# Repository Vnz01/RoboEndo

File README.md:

# How to use?

## Using Two Adafruit M0 Boards

## Receiver MCU:

Program Receiver Side using the code found in /Receiver/ECE using Arduino IDE then plug in to your computer that will be connected to the Maxon Motors

> Optionally you can also do a quick program on platformio using the RF_Head Libary to just quickly read the data and print to serial. I made the switch from Arduino IDE to Platformio mid project, hence why Receiver is programmed through Arduino and Transmitter on platformio

## Transmitter MCU:

Program Transmitter Side using the code found in /Transmitter using Platformio

Edit Latency, I found 10 to work the best giving the controller and receiver to have the best performance.

## Pinout

En - Gnd: Slide Switch (Power Enabling)

13 - Gnd: Lock Switch (Position Control)

12 - Gnd: Momentary Button (Forward)

11 - Gnd: Momentary Button (Backward)

10 - Gnd: Analog Stick Switch (Start Button)

9 - Gnd: Power LED

6 - Gnd: Charging LED

3V3 - Analog Stick Power

GND - Analog Stick GND

A0 - Analog Stick X

A1 - Analog Stick Y

## Computer Side

Using Linux Ubuntu 20.04, install ROS2 Noetic. Download catkin. Following the readme inside /Catheter-Control-main/src/README.md, install the official EPOS Linux Driver. Check the EPOS Command Library PDF. I found the drivers on the japanese maxon motor website after looking at their products. EPOS Studio is for downloading drivers straight to the motors. Then you will be using catkin build not catkin_make to access all the directories. So following the other README located in /Catheter-Control-main/README.md scroll to the bottom. Copy the src file in /Catheter-Control-main to the src file created by catkin build and run your catkin build. To edit the code, look inside the Catheter-Control-main and find control_test.py and edit the if else conditional where NEW CONTROLLER is located.

## ROS Commands

Source the files -
source ~/catkin_ws/devel/setup.bash

Start ROS -
roslaunch maxon_epos_example example_maxon_epos.launch

Run ROSPY -
rosrun maxon_epos_example control_test.py

## Left Off

Controller working properly, there is commented code for a scroll wheel. Pins can be defined to any open pin. It adds to the existing string sent over serial. All the code just needs to be uncommented once scroll wheel is attached.

For the catheter side, look in Catheter-Control-main/src/maxon-epos-example/scripts/old/control_test.py

This file is the edited file and the one we use to control the catheter as we don't have libraries for the main control.py. In this file this is where it is defined for all the movements. To use the controller on your own file it is very modular, just make sure to read input from serial which is a constant string of data that just needs to be parsed.

I left off at implementing the new motor 5 for retracting and protracting. I included a 5th motor in the configuration file in motor_hd.yaml. To implement this, looking inside maxon_epos_driver it seems that it checks how many motors are included and sends commands. You need to define in maxon_epos_example how these commands are sent over ROS and how it will control the 5th motor.

Essentially to get a grasp of this I would restart on a new control_test.py and just read serial values sent by the controller, and try to redefine each movement instead of following the work I have.

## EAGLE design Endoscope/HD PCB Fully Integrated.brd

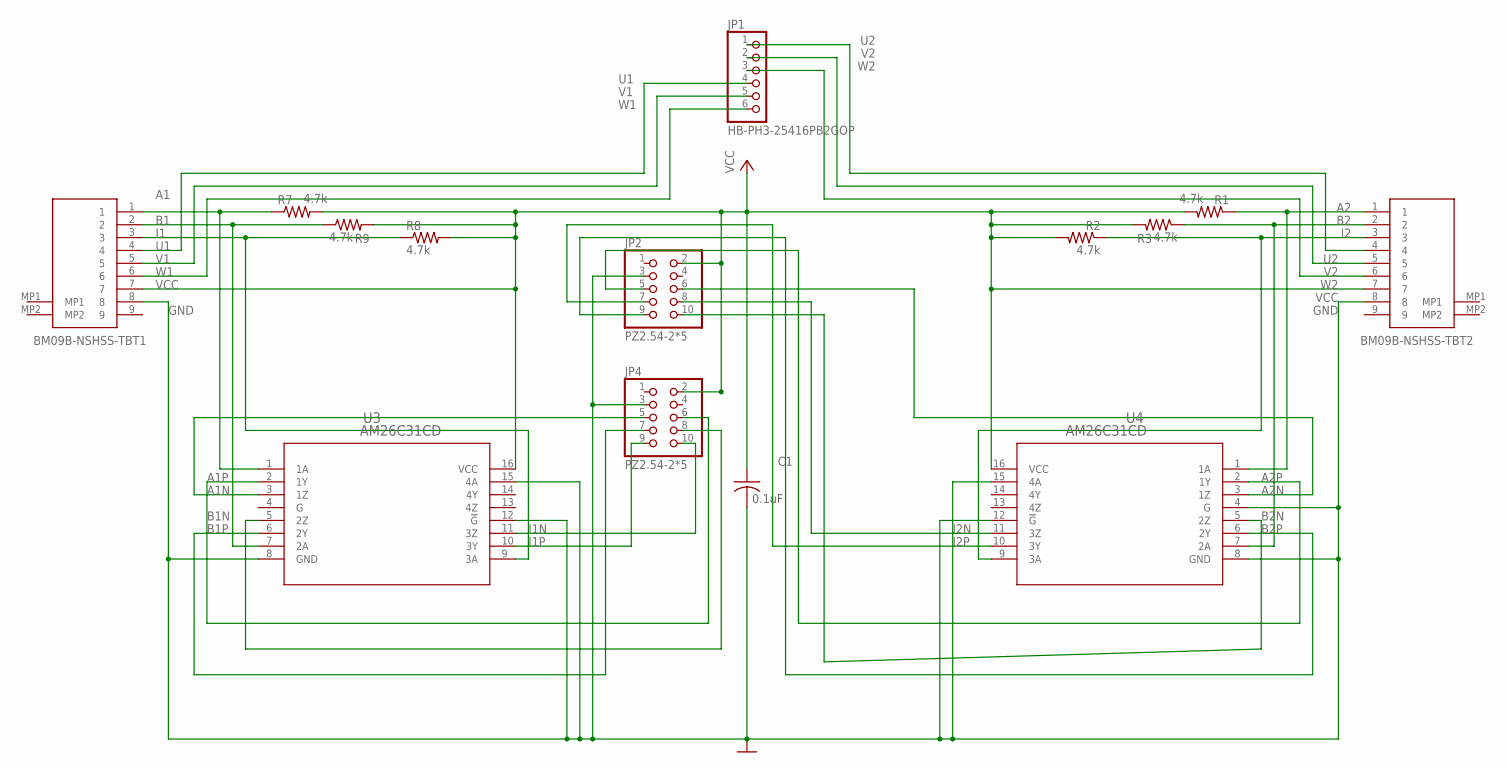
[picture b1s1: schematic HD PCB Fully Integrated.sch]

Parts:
BM09B-NSHSS-TBT1, BM09B-NSHSS-TBT2: BM09B-NSHSS-TBT_LF__SN_; BM09BNSHSSTBTLFSN
C1: 0.1uF; C0805
JP1: HB-PH3-25416PB2GOP; 1X06
JP2, JP4: PZ2.54-2*5; 2X05
R1, R2, R3, R7, R8, R9: 4.7k; R0805; MPN CRCW04024K70FKED
U3, U4: AM26C31CD; D16

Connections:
A1: BM09B-NSHSS-TBT1.1, R7.1, U3.1 (1A)
A1N: JP4.5, U3.3 (1Z)
A1P: JP4.6, U3.2 (1Y)
A2: BM09B-NSHSS-TBT2.1, R1.1, U4.1 (1A)
A2N: JP2.6, U4.3 (1Z)
A2P: JP2.5, U4.2 (1Y)
B1: BM09B-NSHSS-TBT1.2, R9.1, U3.7 (2A)
B1N: JP4.8, U3.5 (2Z)
B1P: JP4.7, U3.6 (2Y)
B2: BM09B-NSHSS-TBT2.2, R3.1, U4.7 (2A)
B2N: JP2.10, U4.5 (2Z)
B2P: JP2.9, U4.6 (2Y)
GND: BM09B-NSHSS-TBT1.8, BM09B-NSHSS-TBT2.8, C1.2, JP2.3, JP4.3, U3.8 (GND), U3.12 (!G), U3.15 (4A), U4.4 (G), U4.8 (GND), U4.12 (!G), U4.15 (4A)
I1: BM09B-NSHSS-TBT1.3, R8.1, U3.9 (3A)
I1N: JP4.10, U3.11 (3Z)
I1P: JP4.9, U3.10 (3Y)
I2: BM09B-NSHSS-TBT2.3, R2.1, U4.9 (3A)
I2N: JP2.8, U4.11 (3Z)
I2P: JP2.7, U4.10 (3Y)
U1: BM09B-NSHSS-TBT1.4, JP1.4
U2: BM09B-NSHSS-TBT2.4, JP1.1
V1: BM09B-NSHSS-TBT1.5, JP1.5
V2: BM09B-NSHSS-TBT2.5, JP1.2
VCC: BM09B-NSHSS-TBT1.7, BM09B-NSHSS-TBT2.7, C1.1, JP2.2, JP4.2, R1.2, R2.2, R3.2, R7.2, R8.2, R9.2, U3.16 (VCC), U4.16 (VCC)
W1: BM09B-NSHSS-TBT1.6, JP1.6
W2: BM09B-NSHSS-TBT2.6, JP1.3

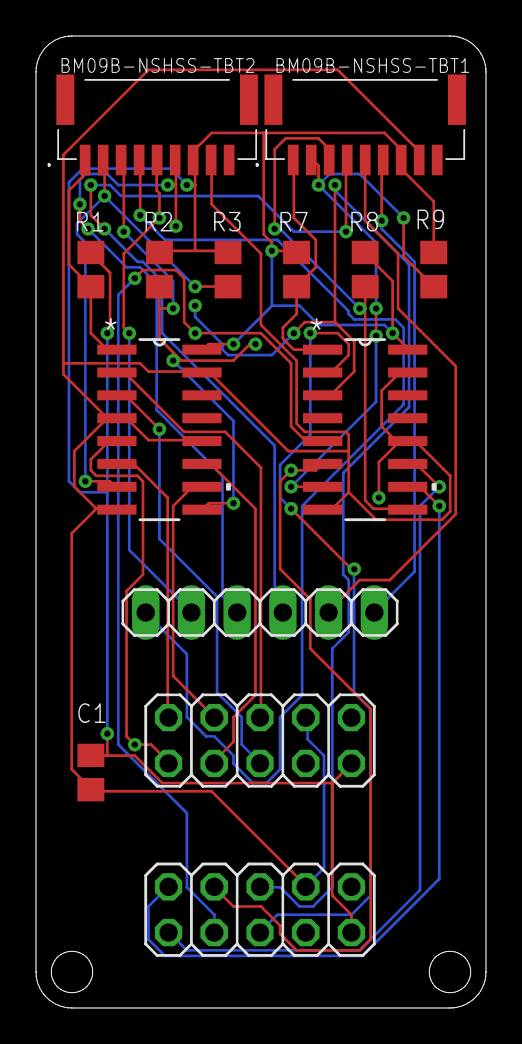
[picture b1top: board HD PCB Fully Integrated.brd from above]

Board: 2 copper layers, 25.0 x 54.0 mm, 14 parts (0 on the bottom side), 26 nets.

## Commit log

2024-02-26 initialize
2024-02-26 Added gitignore
2024-02-26 moving files
2024-02-26 added serialread.py
2024-03-09 Transmitter Code Done
2024-03-09 Added Control.py progress
2024-03-09 Added Receiver ino file
2024-03-09 README.md updated, showing how to use code
2024-03-10 data parsing in py
2024-03-11 Controltest.py updated:
2024-03-13 Fixed code
2024-03-14 LED charging implemented
2024-03-17 Control_test.py updated
2024-03-17 Fixes for controltest
2024-03-21 Final Changes
2024-05-02 Fixed transmitter code for battery led
2024-05-15 Switch encoder added
2024-06-26 Files
2024-07-27 documentation

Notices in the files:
parts and their libraries:
COPYRIGHT: Copyright (C) 2023 Ultra Librarian. All rights reserved.
